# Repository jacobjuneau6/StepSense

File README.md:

# StepSense
StepSense is a pod that attaches to a shoe and warns the wearer through an audible alarm that they are about to walk into something.
# Why
I made this project after seeing many of my friends and myselfwalk into wallsor other obstacleswhilelooking down at a phone. The idea is that it rests on the shoe and warns the wearer of a potential obstacle.
# Pictures

# BOM
| Reference | Qty | Footprint | Link | Supplier |
| --- | --- | --- | --- | --- |
| B1 | 1 | Connector_PinHeader_1.00mm:PinHeader_1x02_P1.00mm_Horizontal | https://www.amazon.com/YTKavq-Battery-Lithium-Rechargeable-Connector/dp/B08TTXX1W4?s=electronics | Amazon |
| LS1 | 1 | PS1240P02BT:XDCR_PS1240P02BT | https://www.aliexpress.us/item/3256808371712170.html?utparam-url=scene%3Asearch%7Cquery_from%3A%7Cx_object_id%3A1005008558026922%7C_p_origin_prod%3A1005008129032384 | Aliexpress |
| M1 | 1 | Connector_PinHeader_2.54mm:PinHeader_1x06_P2.54mm_Horizontal | https://www.aliexpress.us/item/3256806005285334.html?utparam-url=scene%3Asearch%7Cquery_from%3A%7Cx_object_id%3A1005006191600086%7C_p_origin_prod%3A | Aliexpress |
| Q1 | 1 | 2N2222:TO127P584H533-3 | https://www.aliexpress.us/item/3256807891334673.html?utparam-url=scene%3Asearch%7Cquery_from%3A%7Cx_object_id%3A1005008077649425%7C_p_origin_prod%3A1005009744071978 | Aliexpress |
| R1,R2,R3 | 3 | Resistor_THT:R_Axial_DIN0207_L6.3mm_D2.5mm_P10.16mm_Horizontal | https://www.amazon.com/Avelis-Resistors-Assortment-Precision-Electronic/dp/B0FNRD8B3X | Amazon |
| U1 | 1 | XIAO_ESP32C3:xiao_esp32c3 | https://www.seeedstudio.com/Seeed-Studio-XIAO-ESP32C3-Tape-Reel-p-6471.html | Seeed Technology |
| Custom PCB | 1 | | PCB-v1/ | PCBWAY |

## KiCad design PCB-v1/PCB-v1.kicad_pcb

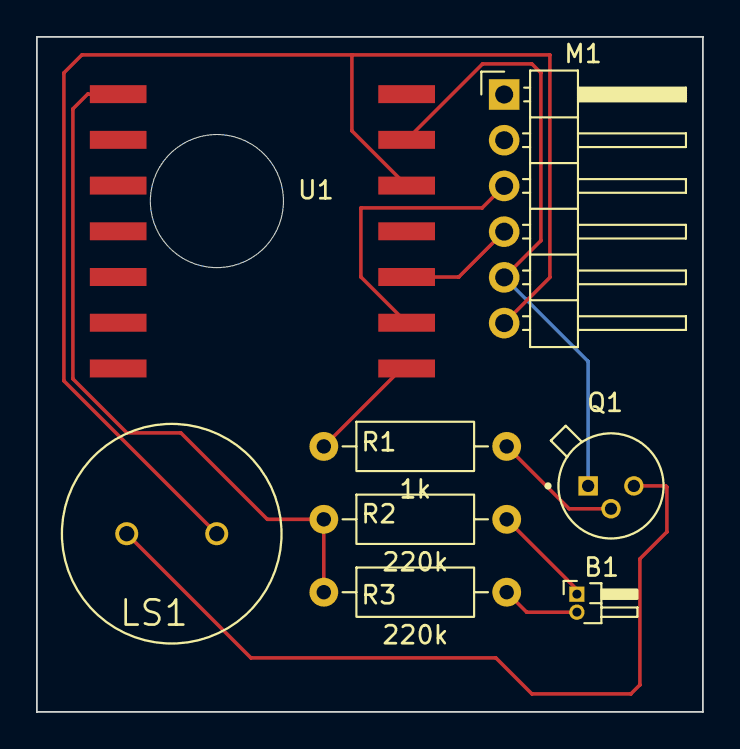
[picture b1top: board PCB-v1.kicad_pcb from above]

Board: 2 copper layers, 37.0 x 37.5 mm, 8 parts (0 on the bottom side), 10 nets.

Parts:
B1: PinHeader_1x02_P1.00mm_Horizontal
LS1: PS1240P02BT; XDCR_PS1240P02BT
M1: PinHeader_1x06_P2.54mm_Horizontal
Q1: 2N2222; TO127P584H533-3
R1: 1k; R_Axial_DIN0207_L6.3mm_D2.5mm_P10.16mm_Horizontal
R2, R3: 220k; R_Axial_DIN0207_L6.3mm_D2.5mm_P10.16mm_Horizontal
U1: XIAO ESP32C3; xiao_esp32c3

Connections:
unnamed: B1.1 (+), R2.2
unnamed: B1.2 (-), R3.2
unnamed: LS1.1, Q1.3
unnamed: M1.5 (GND), Q1.1, U1.13 (GND)
unnamed: M1.4 (SCL), U1.10 (D9)
unnamed: M1.3 (SDA), U1.9 (D8)
unnamed: LS1.2, M1.6 (VIN), U1.12 (VCC_3V3)
unnamed: Q1.2, R1.2
unnamed: R2.1, R3.1, U1.1 (D0)
unnamed: R1.1, U1.8 (D7)

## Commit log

2026-03-14 Add workspace file
2026-03-14 PCB-v1 design
2026-03-14 Add CAD and CODE
2026-03-15 ADD BOM
2026-03-15 pictures
2026-03-15 update stl from cad
2026-03-15 updated slicer files
